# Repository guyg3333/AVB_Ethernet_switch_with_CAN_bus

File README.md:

# AVB_Ethernet_switch_with_CAN_bus

This PCB was made As part of an Academic engineering final project, the idea behind it is to offer a method of reorganizing information traffic in autonomous vehicles,

The problem I wanted to solve is how to expand the current communication method to support Advanced Drive assist application.

The proposed solution is to build a network built from a combination of CAN bus and Ethernet interfaces, were Ethernet used as backbone.

To do so I design and implement module that aim to manage data traffic and with him create a hierarchical Democratic multi master network were every node can exchange data.

To meet the requirements of critical information passing through a vehicle, the Ethernet switch ic supports the AVB protocol to Ensure real time policy.

The component was assimilated in Ben-Gurion University FSAE electric car in 2019

## PCB 3D Model

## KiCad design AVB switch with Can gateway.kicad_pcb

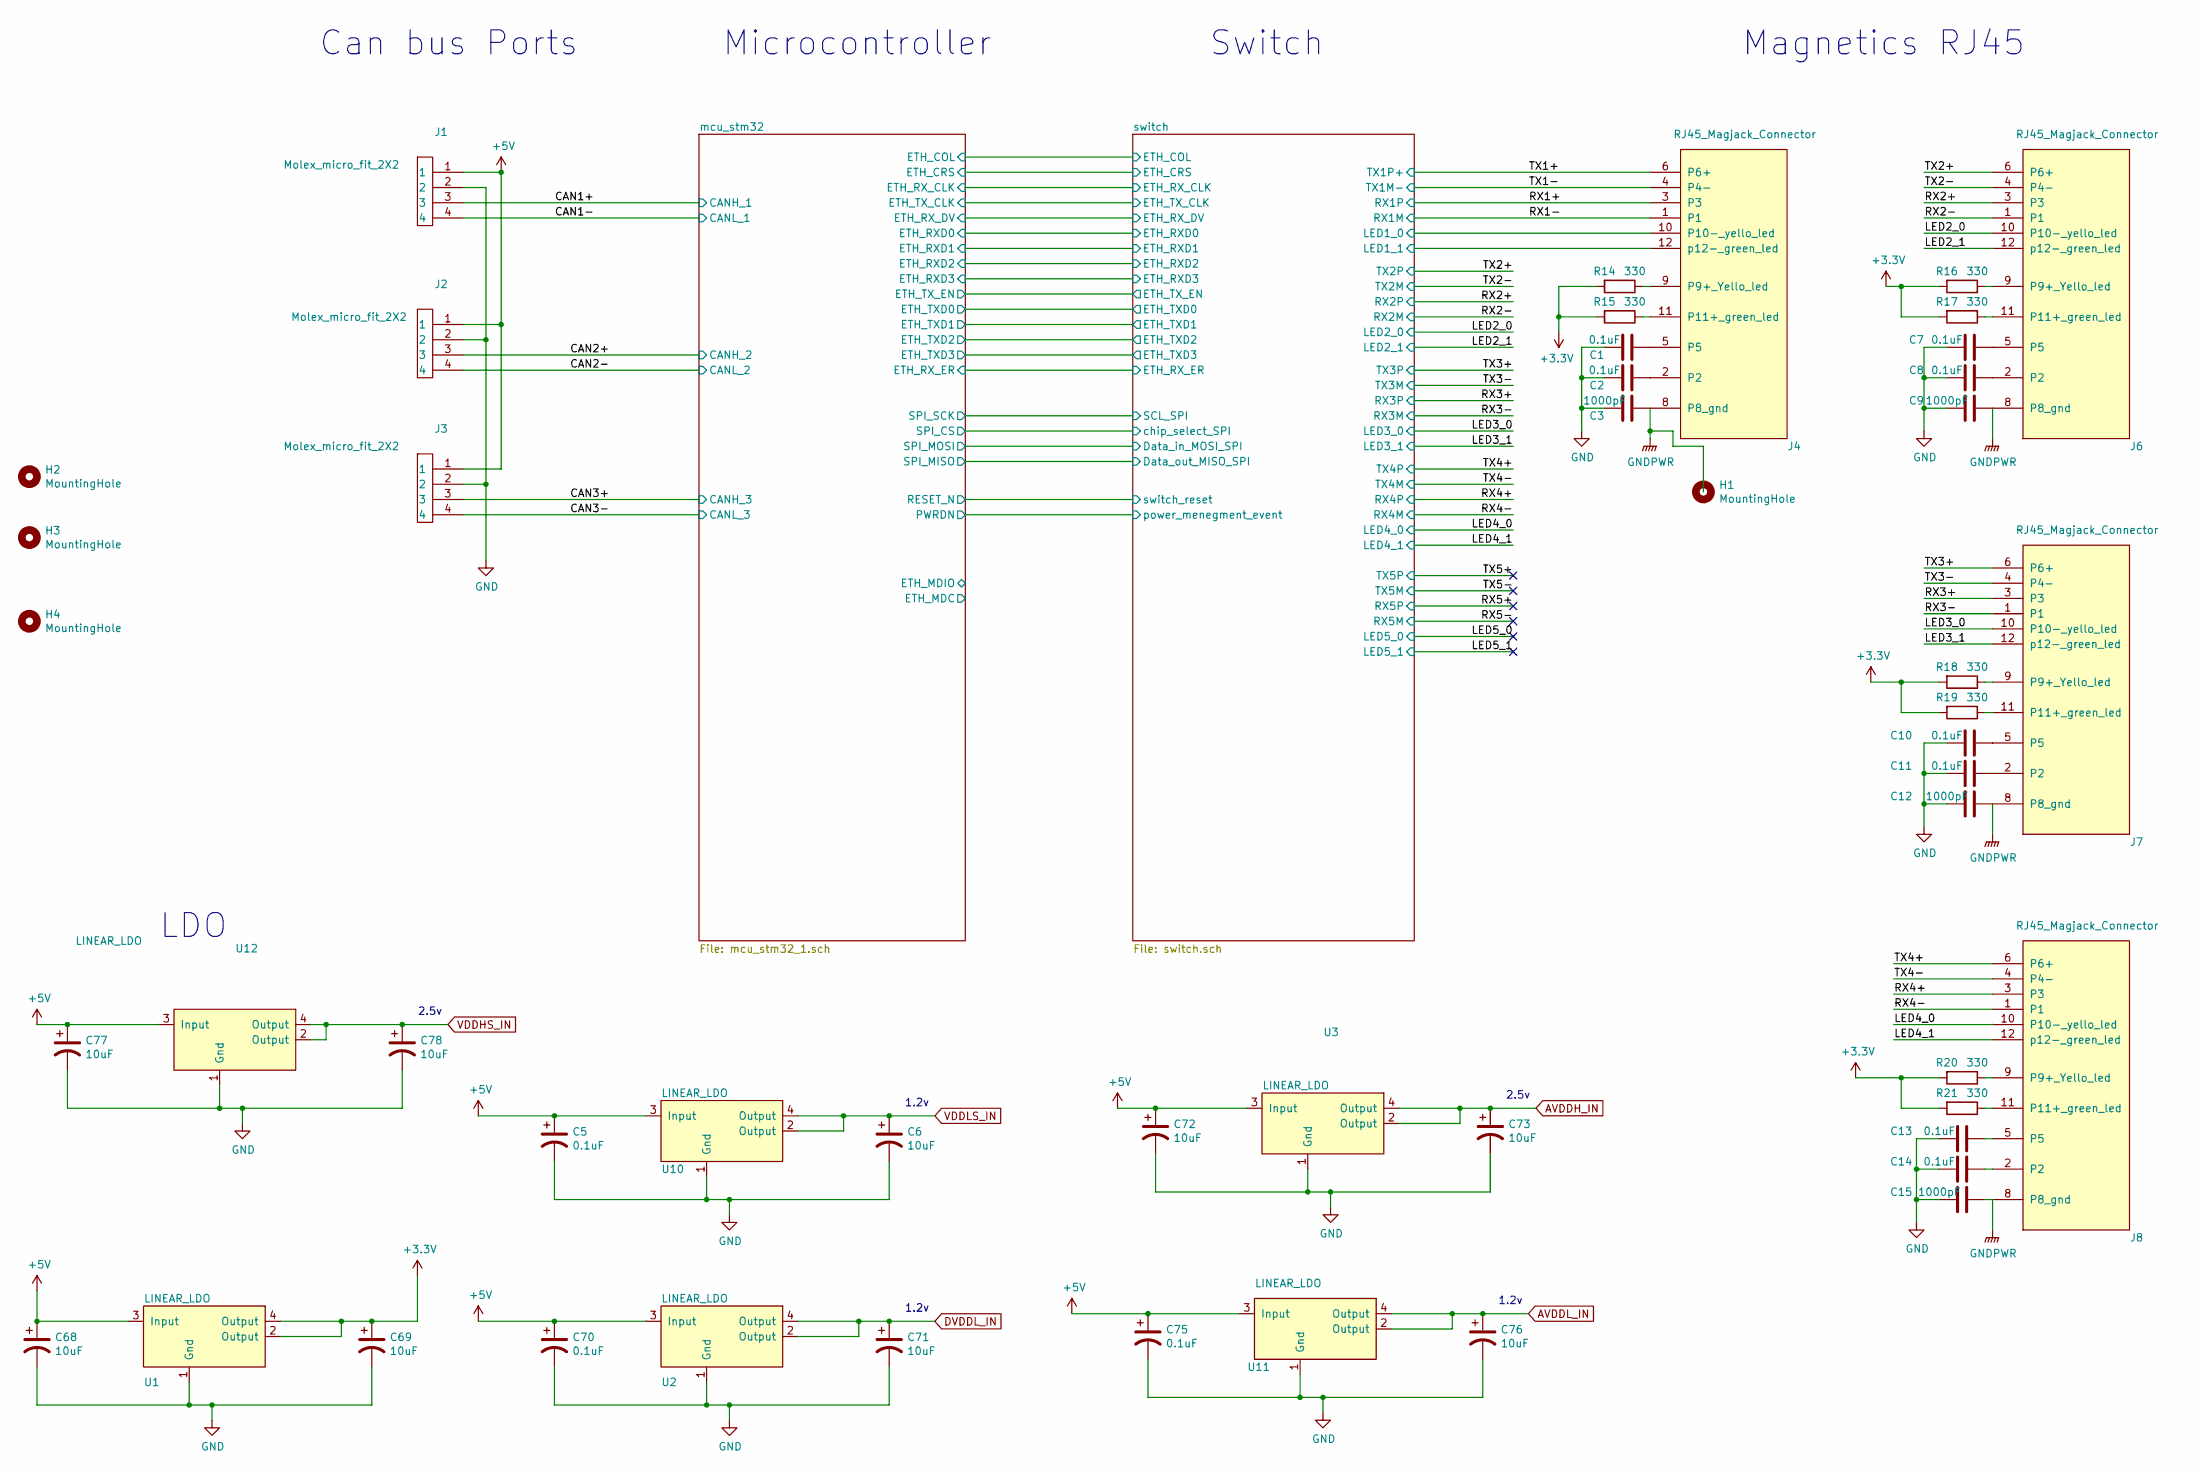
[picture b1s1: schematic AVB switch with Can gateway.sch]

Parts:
C1, C2, C7, C8, C10, C11, C13, C14: 0.1uF; C_0603_1608Metric_Pad1.05x0.95mm_HandSolder; Manufacturer_Part_Number C0603C104J4RACTU‎‏
C3, C9, C12, C15: 1000pF; C_0603_1608Metric_Pad1.05x0.95mm_HandSolder; Manufacturer_Part_Number C0603V102KDRAC7867‎‏
C5, C70, C75: 0.1uF; C_0603_1608Metric_Pad1.05x0.95mm_HandSolder; Manufacturer_Part_Number CC1206KRX7R9BB104‎‏
C6, C68, C69, C71, C72, C73, C76, C77, C78: 10uF; C_0603_1608Metric_Pad1.05x0.95mm_HandSolder; Manufacturer_Part_Number T520A106M010ATE080‎‏
H1, H2, H3, H4: MountingHole; 1pin
J1, J2, J3: Molex_micro_fit_2X2; Manufacturer_Part_Number ‏‎CONN HEADER VERT 4POS 3MM‎‏
J4, J6, J7, J8: RJ45_Magjack_Connector; RJ45_MAGJACK_1PORT_100_BASE-T‎‏; Manufacturer_Part_Number ‏‎JD2-0010NL‎‏
R14, R15, R16, R17, R18, R19, R20, R21: 330; R_0603_1608Metric_Pad1.05x0.95mm_HandSolder; Manufacturer_Part_Number ‏‎CR0603-JW-331ELF‎‏
U1: LINEAR_LDO; SOT-223; Manufacturer_Part_Number NCP1117ST33T3G‎‏
U2, U10, U11: LINEAR_LDO; SOT-223; Manufacturer_Part_Number LD1117AS12TR‎‏
U3, U12: LINEAR_LDO; SOT-223; Manufacturer_Part_Number ‏‎NCV1117ST25T3G‎‏

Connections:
+3V3: C69.1, R14.2, R15.2, R16.2, R17.2, R18.2, R19.2, R20.2, R21.2, U1.2 (Output), U1.4 (Output); also elsewhere on the board
+5V: C5.1, C68.1, C70.1, C72.1, C75.1, C77.1, J1.1, J2.1, J3.1, U1.3 (Input), U2.3 (Input), U3.3 (Input), U10.3 (Input), U11.3 (Input), U12.3 (Input)
/CAN1+: J1.3; also elsewhere on the board
/CAN1-: J1.4; also elsewhere on the board
/CAN2+: J2.3; also elsewhere on the board
/CAN2-: J2.4; also elsewhere on the board
/CAN3+: J3.3; also elsewhere on the board
/CAN3-: J3.4; also elsewhere on the board
/LED2_0: J6.10 (P10-_yello_led); also elsewhere on the board
/LED2_1: J6.12 (p12-_green_led); also elsewhere on the board
/LED3_0: J7.10 (P10-_yello_led); also elsewhere on the board
/LED3_1: J7.12 (p12-_green_led); also elsewhere on the board
/LED4_0: J8.10 (P10-_yello_led); also elsewhere on the board
/LED4_1: J8.12 (p12-_green_led); also elsewhere on the board
/RX1+: J4.3; also elsewhere on the board
/RX1-: J4.1; also elsewhere on the board
/RX2+: J6.3; also elsewhere on the board
/RX2-: J6.1; also elsewhere on the board
/RX3+: J7.3; also elsewhere on the board
/RX3-: J7.1; also elsewhere on the board
/RX4+: J8.3; also elsewhere on the board
/RX4-: J8.1; also elsewhere on the board
/TX1+: J4.6 (P6+); also elsewhere on the board
/TX1-: J4.4 (P4-); also elsewhere on the board
/TX2+: J6.6 (P6+); also elsewhere on the board
/TX2-: J6.4 (P4-); also elsewhere on the board
/TX3+: J7.6 (P6+); also elsewhere on the board
/TX3-: J7.4 (P4-); also elsewhere on the board
/TX4+: J8.6 (P6+); also elsewhere on the board
/TX4-: J8.4 (P4-); also elsewhere on the board
/switch/LED1_0: J4.10 (P10-_yello_led); also elsewhere on the board
/switch/LED1_1: J4.12 (p12-_green_led); also elsewhere on the board
AVDDH_IN: C73.1, U3.2 (Output), U3.4 (Output); also elsewhere on the board
AVDDL_IN: C76.1, U11.2 (Output), U11.4 (Output); also elsewhere on the board
DVDDL_IN: C71.1, U2.2 (Output), U2.4 (Output); also elsewhere on the board
GND: C1.2, C2.2, C3.2, C5.2, C6.2, C7.2, C8.2, C9.2, C10.2, C11.2, C12.2, C13.2, C14.2, C15.2, C68.2, C69.2, C70.2, C71.2, C72.2, C73.2, C75.2, C76.2, C77.2, C78.2, J1.2, J2.2, J3.2, U1.1 (Gnd), U2.1 (Gnd), U3.1 (Gnd), U10.1 (Gnd), U11.1 (Gnd), U12.1 (Gnd); also elsewhere on the board
GNDPWR: C3.1, C9.1, C12.1, C15.1, J4.8 (P8_gnd), J6.8 (P8_gnd), J7.8 (P8_gnd), J8.8 (P8_gnd)
unnamed: C1.1, J4.5
unnamed: C2.1, J4.2
unnamed: C7.1, J6.5
unnamed: C8.1, J6.2
unnamed: C10.1, J7.5
unnamed: C11.1, J7.2
unnamed: C13.1, J8.5
unnamed: C14.1, J8.2
unnamed: J4.9 (P9+_Yello_led), R14.1
unnamed: J4.11 (P11+_green_led), R15.1
unnamed: J6.9 (P9+_Yello_led), R16.1
unnamed: J6.11 (P11+_green_led), R17.1
unnamed: J7.9 (P9+_Yello_led), R18.1
unnamed: J7.11 (P11+_green_led), R19.1
unnamed: J8.9 (P9+_Yello_led), R20.1
unnamed: J8.11 (P11+_green_led), R21.1
VDDHS_IN: C78.1, U12.2 (Output), U12.4 (Output); also elsewhere on the board
VDDLS_IN: C6.1, U10.2 (Output), U10.4 (Output); also elsewhere on the board

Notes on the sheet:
Switch
Microcontroller
Can bus Ports
Magnetics RJ45
LDO
2.5v
1.2v

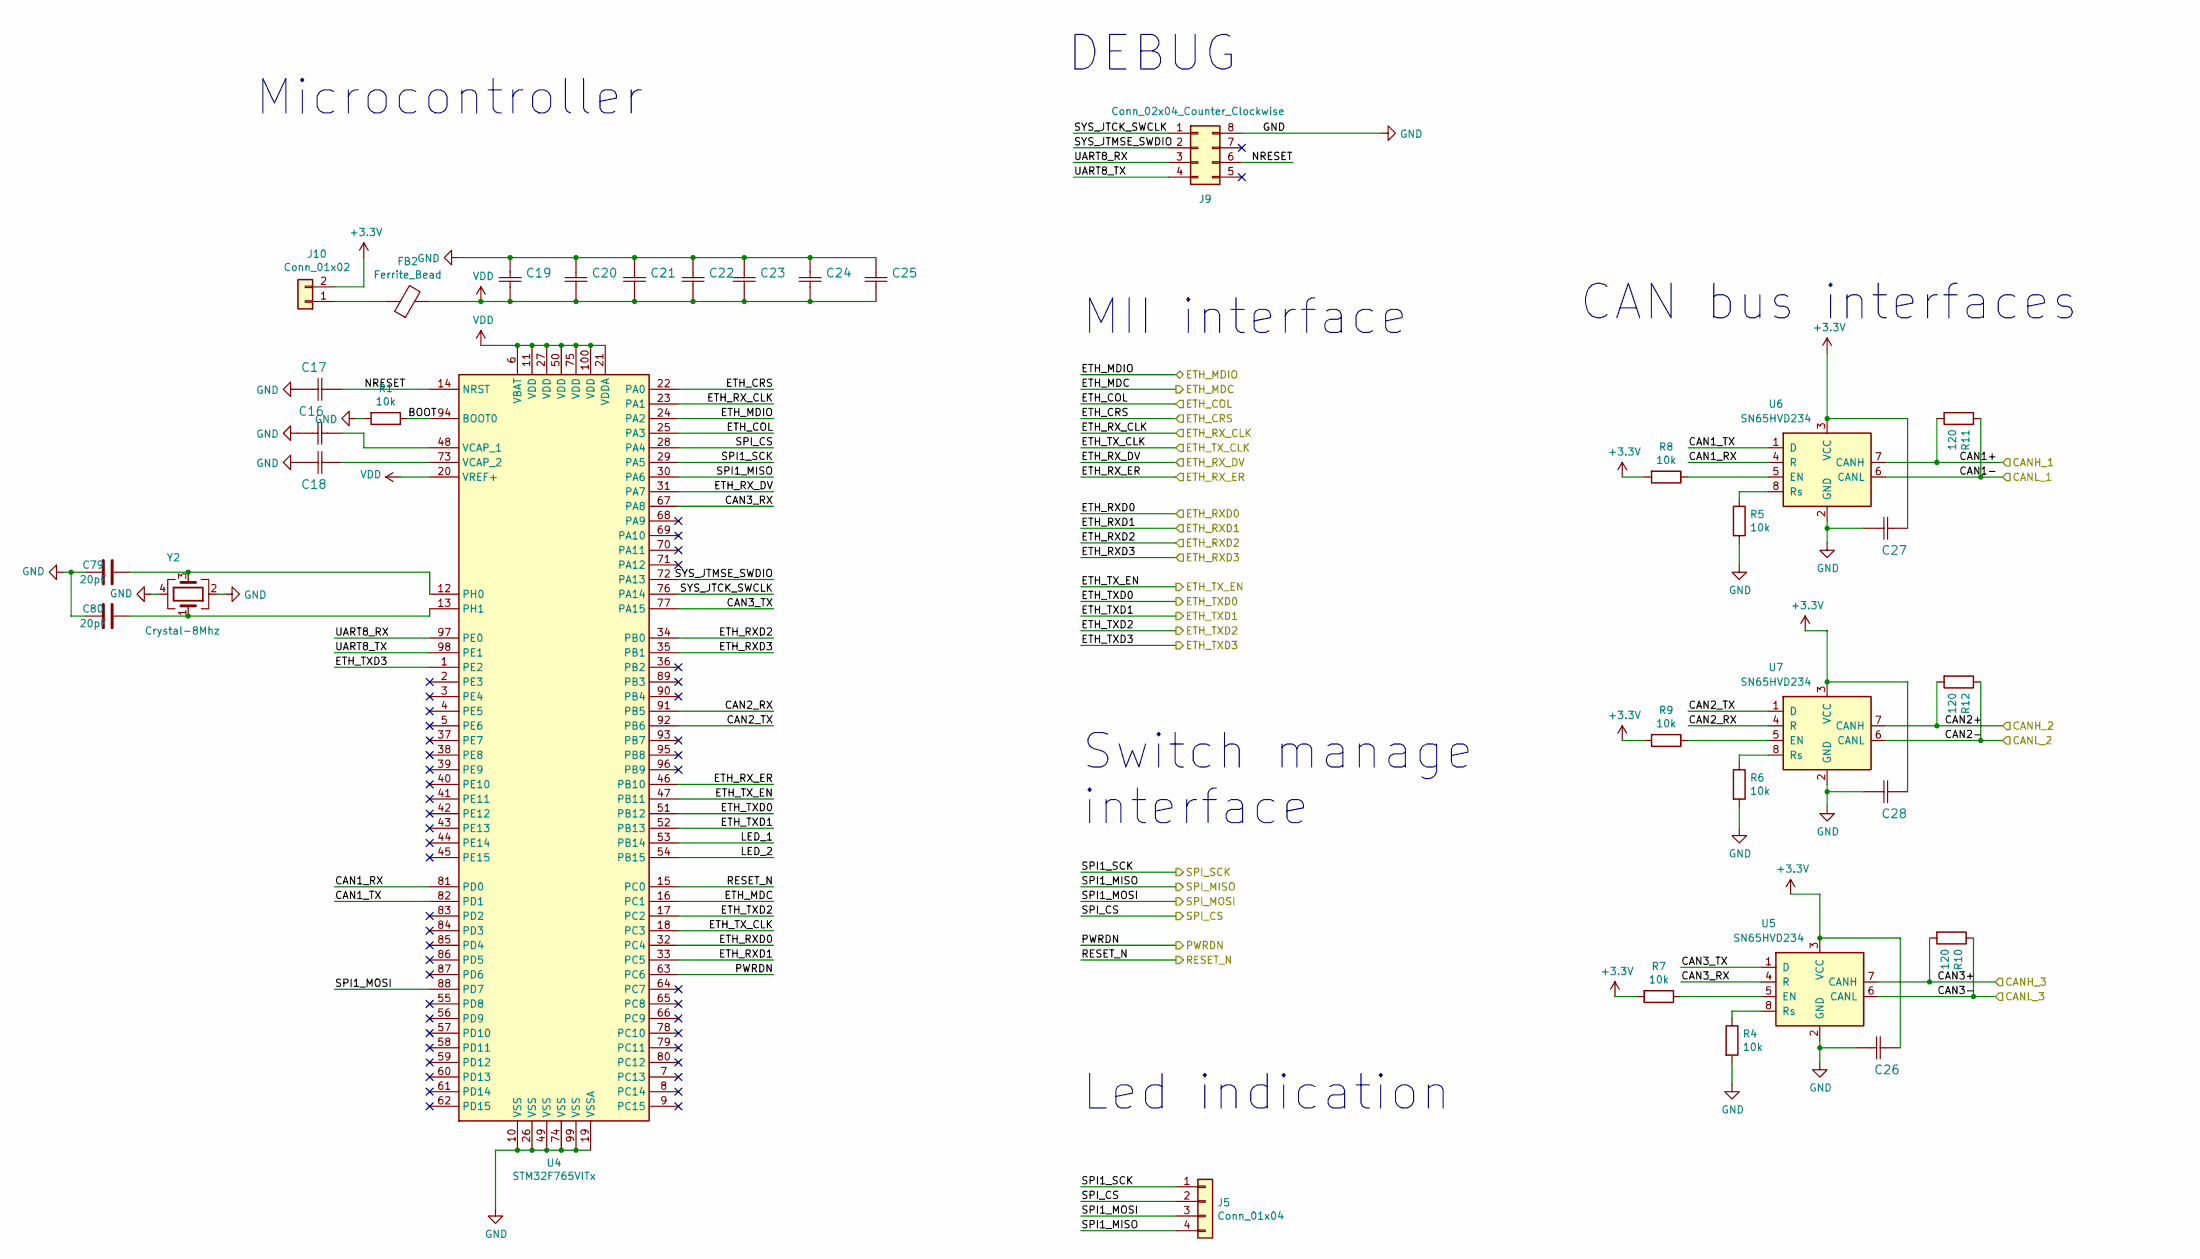
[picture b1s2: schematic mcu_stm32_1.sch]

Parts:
C16, C18, C26, C27, C28: 2.2uF; C_0603_1608Metric_Pad1.05x0.95mm_HandSolder; Manufacturer_Part_Number CL10A225KP8NNNC‎‏
C17, C20, C21, C22, C23, C24, C25: 0.1uF; C_0603_1608Metric_Pad1.05x0.95mm_HandSolder; Manufacturer_Part_Number C0603C104J4RACTU‎‏
C19: 4.7uF; C_0603_1608Metric_Pad1.05x0.95mm_HandSolder; Manufacturer_Part_Number CL10B475KQ8NQNC‎‏
C79, C80: 20pF; C_0603_1608Metric_Pad1.05x0.95mm_HandSolder; Manufacturer_Part_Number CL10C360JB8NNNC‎‏
FB2: Ferrite_Bead; C_0603_1608Metric_Pad1.05x0.95mm_HandSolder
J5: Conn_01x04; PinHeader_1x04_P2.54mm_Vertical
J9: Conn_02x04_Counter_Clockwise; PinHeader_2x04_P2.54mm_Vertical
J10: Conn_01x02; PinHeader_1x02_P2.54mm_Vertical
R1: 10k; R_0603_1608Metric_Pad1.05x0.95mm_HandSolder
R4, R5, R6, R7, R8, R9: 10k; R_0603_1608Metric_Pad1.05x0.95mm_HandSolder; Manufacturer_Part_Number RNCP0603FTD10K0‎‏
R10, R11, R12: 120; R_0603_1608Metric_Pad1.05x0.95mm_HandSolder; Manufacturer_Part_Number ‏‎CRGCQ0603F120R‎‏
U4: STM32F765VITx; LQFP-100_14x14mm_P0.5mm; Manufacturer_Part_Number ‏‎STM32F765VIT6‎‏
U5, U6, U7: SN65HVD234; SOIC-8_3.9x4.9mm_P1.27mm; Manufacturer_Part_Number SN65HVD234DR‎‏
Y2: Crystal-8Mhz; Crystal_SMD_3225-4Pin_3.2x2.5mm; Manufacturer_Part_Number ‏‎ECS-80-10-30B-CWN-TR‎‏

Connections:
+3V3: C26.1, C27.1, C28.1, J10.2, R7.2, R8.2, R9.2, U5.3 (VCC), U6.3 (VCC), U7.3 (VCC); also elsewhere on the board
/CAN1+: R11.2, U6.7 (CANH); also elsewhere on the board
/CAN1-: R11.1, U6.6 (CANL); also elsewhere on the board
/CAN2+: R12.2, U7.7 (CANH); also elsewhere on the board
/CAN2-: R12.1, U7.6 (CANL); also elsewhere on the board
/CAN3+: R10.2, U5.7 (CANH); also elsewhere on the board
/CAN3-: R10.1, U5.6 (CANL); also elsewhere on the board
/mcu_stm32/BOOT: R1.1, U4.94 (BOOT0)
/mcu_stm32/CAN1_RX: U4.81 (PD0), U6.4 (R)
/mcu_stm32/CAN1_TX: U4.82 (PD1), U6.1 (D)
/mcu_stm32/CAN2_RX: U4.91 (PB5), U7.4 (R)
/mcu_stm32/CAN2_TX: U4.92 (PB6), U7.1 (D)
/mcu_stm32/CAN3_RX: U4.67 (PA8), U5.4 (R)
/mcu_stm32/CAN3_TX: U4.77 (PA15), U5.1 (D)
/mcu_stm32/ETH_COL: U4.25 (PA3); also elsewhere on the board
/mcu_stm32/ETH_CRS: U4.22 (PA0); also elsewhere on the board
/mcu_stm32/ETH_MDC: U4.16 (PC1)
/mcu_stm32/ETH_MDIO: U4.24 (PA2)
/mcu_stm32/ETH_RXD0: U4.32 (PC4); also elsewhere on the board
/mcu_stm32/ETH_RXD1: U4.33 (PC5); also elsewhere on the board
/mcu_stm32/ETH_RXD2: U4.34 (PB0); also elsewhere on the board
/mcu_stm32/ETH_RXD3: U4.35 (PB1); also elsewhere on the board
/mcu_stm32/ETH_RX_CLK: U4.23 (PA1); also elsewhere on the board
/mcu_stm32/ETH_RX_DV: U4.31 (PA7); also elsewhere on the board
/mcu_stm32/ETH_RX_ER: U4.46 (PB10); also elsewhere on the board
/mcu_stm32/ETH_TXD0: U4.51 (PB12); also elsewhere on the board
/mcu_stm32/ETH_TXD1: U4.52 (PB13); also elsewhere on the board
/mcu_stm32/ETH_TXD2: U4.17 (PC2); also elsewhere on the board
/mcu_stm32/ETH_TXD3: U4.1 (PE2); also elsewhere on the board
/mcu_stm32/ETH_TX_CLK: U4.18 (PC3); also elsewhere on the board
/mcu_stm32/ETH_TX_EN: U4.47 (PB11); also elsewhere on the board
/mcu_stm32/LED_1: U4.53 (PB14)
/mcu_stm32/LED_2: U4.54 (PB15)
/mcu_stm32/NRESET: C17.1, J9.6, U4.14 (NRST)
/mcu_stm32/PWRDN: U4.63 (PC6)
/mcu_stm32/RESET_N: U4.15 (PC0); also elsewhere on the board
/mcu_stm32/SPI_CS: J5.2, U4.28 (PA4); also elsewhere on the board
/mcu_stm32/SYS_JTCK_SWCLK: J9.1, U4.76 (PA14)
/mcu_stm32/SYS_JTMSE_SWDIO: J9.2, U4.72 (PA13)
/mcu_stm32/UART8_RX: J9.3, U4.97 (PE0)
/mcu_stm32/UART8_TX: J9.4, U4.98 (PE1)
/switch/Data_in_MOSI_SPI: J5.3, U4.88 (PD7); also elsewhere on the board
/switch/Data_out_MISO_SPI: J5.4, U4.30 (PA6); also elsewhere on the board
/switch/SCL_SPI: J5.1, U4.29 (PA5); also elsewhere on the board
GND: C16.1, C17.2, C18.2, C19.1, C20.1, C21.1, C22.1, C23.1, C24.1, C25.1, C26.2, C27.2, C28.2, C79.2, C80.2, J9.8, R1.2, R4.2, R5.2, R6.2, U4.10 (VSS), U4.19 (VSSA), U4.26 (VSS), U4.49 (VSS), U4.74 (VSS), U4.99 (VSS), U5.2 (GND), U6.2 (GND), U7.2 (GND), Y2.2, Y2.4; also elsewhere on the board
unnamed: C16.2, U4.48 (VCAP_1)
unnamed: C18.1, U4.73 (VCAP_2)
unnamed: C79.1, U4.12 (PH0), Y2.3
unnamed: C80.1, U4.13 (PH1), Y2.1
unnamed: FB2.1, J10.1
unnamed: R4.1, U5.8 (Rs)
unnamed: R5.1, U6.8 (Rs)
unnamed: R6.1, U7.8 (Rs)
unnamed: R7.1, U5.5 (EN)
unnamed: R8.1, U6.5 (EN)
unnamed: R9.1, U7.5 (EN)
VDD: C19.2, C20.2, C21.2, C22.2, C23.2, C24.2, C25.2, FB2.2, U4.6 (VBAT), U4.11 (VDD), U4.20 (VREF+), U4.21 (VDDA), U4.27 (VDD), U4.50 (VDD), U4.75 (VDD), U4.100 (VDD)

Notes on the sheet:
DEBUG
MII interface
CAN bus interfaces
Microcontroller
Switch manage interface
Led indication

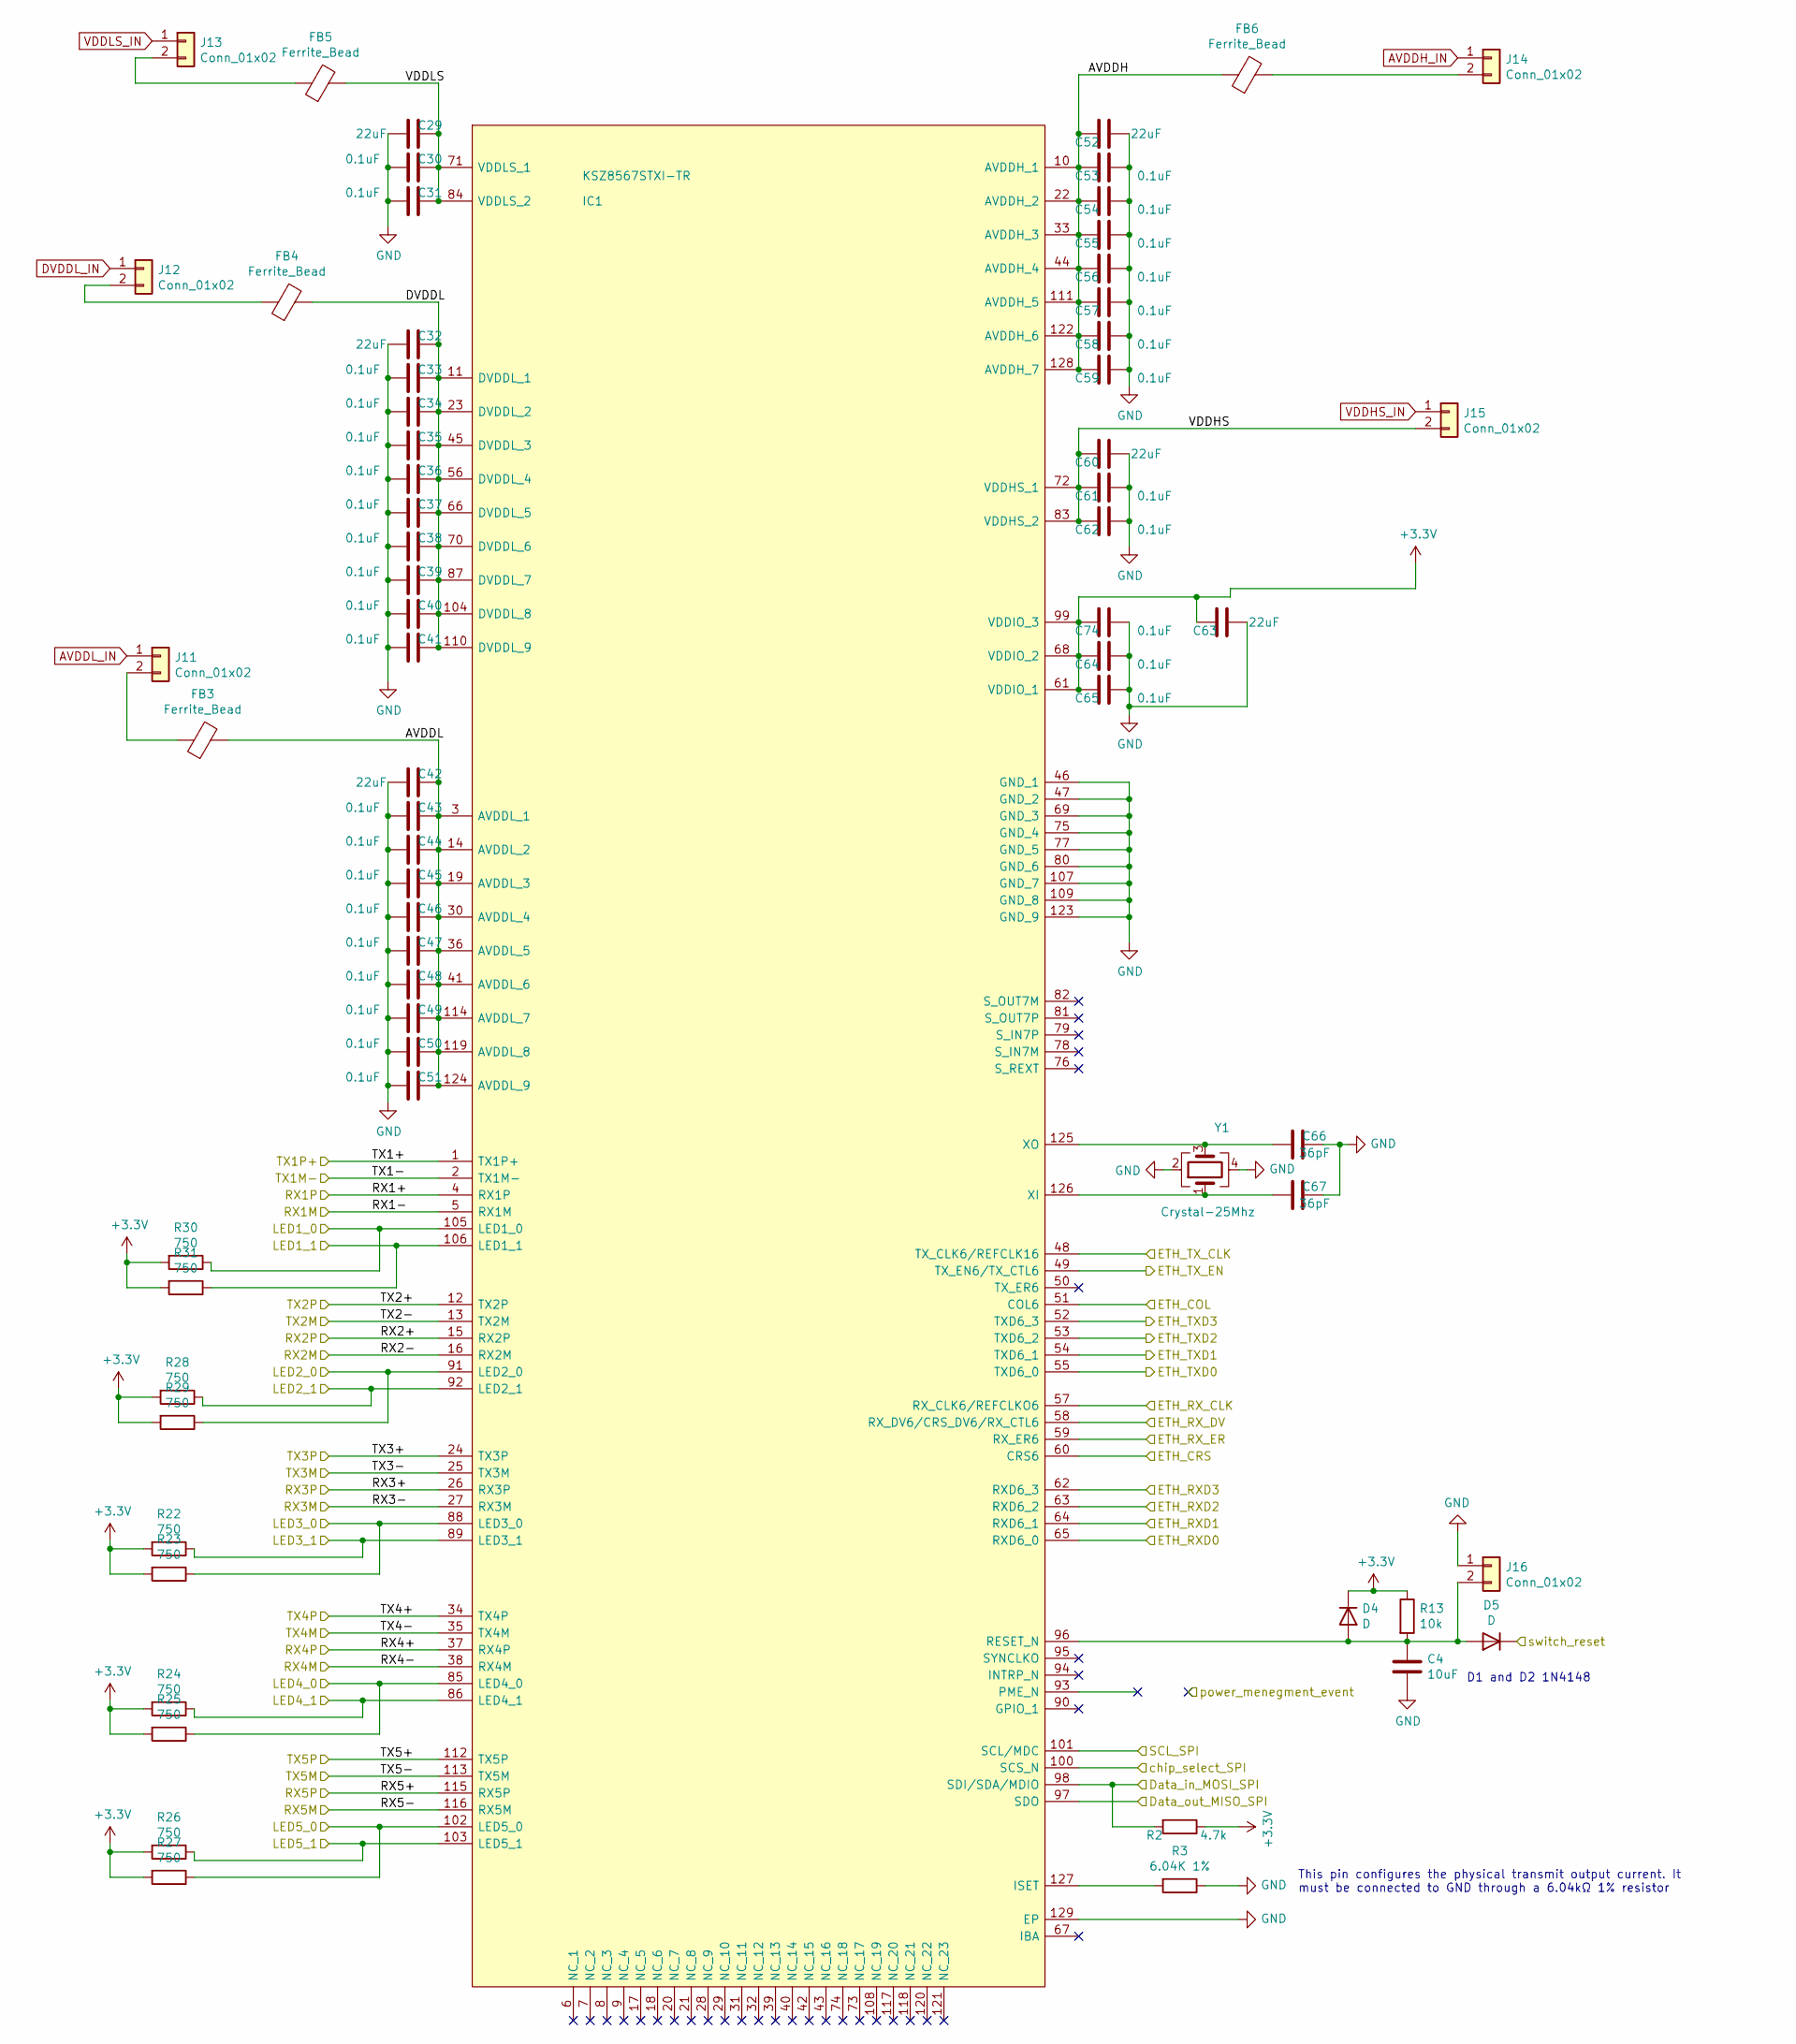
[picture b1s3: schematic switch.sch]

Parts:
C4: 10uF; C_0603_1608Metric_Pad1.05x0.95mm_HandSolder; Manufacturer_Part_Number CL10A106MQ8NNNC‎‏
C29, C32, C42, C52, C60, C63: 22uF; C_0603_1608Metric_Pad1.05x0.95mm_HandSolder; Manufacturer_Part_Number C1608X5R0J226M080AC‎‏
C30, C31, C33, C34, C35, C36, C37, C38, C39, C40, C41, C43, C44, C45, C46, C47, C48, C49, C50, C51, C53, C54, C55, C56, C57, C58, C59, C61, C62, C64, C65, C74: 0.1uF; C_0603_1608Metric_Pad1.05x0.95mm_HandSolder; Manufacturer_Part_Number C0603C104J4RACTU‎‏
C66, C67: 36pF; C_0603_1608Metric_Pad1.05x0.95mm_HandSolder; Manufacturer_Part_Number CL10C360JB8NNNC‎‏
D4, D5: D; D_SOD-323_HandSoldering; Manufacturer_Part_Number 1N4148WXTPMSCT
FB3, FB4, FB5, FB6: Ferrite_Bead; C_0603_1608Metric_Pad1.05x0.95mm_HandSolder
IC1: KSZ8567STXI-TR; QFP40P1600X1600X120-129N; Mouser Part Number 579-KSZ8567STXI-TR
J11, J12, J13, J14, J15, J16: Conn_01x02; PinHeader_1x02_P2.54mm_Vertical
R2: 4.7k; R_0603_1608Metric_Pad1.05x0.95mm_HandSolder; Manufacturer_Part_Number ‏‎RC0603JR-074K7L‎‏
R3: 6.04K 1%; R_0603_1608Metric_Pad1.05x0.95mm_HandSolder; Manufacturer_Part_Number RMCF0603FT6K04‎‏
R13: 10k; R_0603_1608Metric_Pad1.05x0.95mm_HandSolder; Manufacturer_Part_Number RNCP0603FTD10K0‎‏
R22, R23, R24, R25, R26, R27, R28, R29, R30, R31: 750; R_0603_1608Metric_Pad1.05x0.95mm_HandSolder
Y1: Crystal-25Mhz; Crystal_SMD_3225-4Pin_3.2x2.5mm; Manufacturer_Part_Number ‏‎FA-238 25.0000MB-C3‎‏

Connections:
+3V3: C63.1, C64.1, C65.1, C74.1, D4.1 (K), IC1.61 (VDDIO_1), IC1.68 (VDDIO_2), IC1.99 (VDDIO_3), R2.1, R13.1, R22.2, R23.2, R24.2, R25.2, R26.2, R27.2, R28.2, R29.2, R30.2, R31.2; also elsewhere on the board
/LED2_0: IC1.91 (LED2_0), R29.1; also elsewhere on the board
/LED2_1: IC1.92 (LED2_1), R28.1; also elsewhere on the board
/LED3_0: IC1.88 (LED3_0), R23.1; also elsewhere on the board
/LED3_1: IC1.89 (LED3_1), R22.1; also elsewhere on the board
/LED4_0: IC1.85 (LED4_0), R25.1; also elsewhere on the board
/LED4_1: IC1.86 (LED4_1), R24.1; also elsewhere on the board
/LED5_0: IC1.102 (LED5_0), R27.1
/LED5_1: IC1.103 (LED5_1), R26.1
/RX1+: IC1.4 (RX1P); also elsewhere on the board
/RX1-: IC1.5 (RX1M); also elsewhere on the board
/RX2+: IC1.15 (RX2P); also elsewhere on the board
/RX2-: IC1.16 (RX2M); also elsewhere on the board
/RX3+: IC1.26 (RX3P); also elsewhere on the board
/RX3-: IC1.27 (RX3M); also elsewhere on the board
/RX4+: IC1.37 (RX4P); also elsewhere on the board
/RX4-: IC1.38 (RX4M); also elsewhere on the board
/RX5+: IC1.115 (RX5P)
/RX5-: IC1.116 (RX5M)
/TX1+: IC1.1 (TX1P+); also elsewhere on the board
/TX1-: IC1.2 (TX1M-); also elsewhere on the board
/TX2+: IC1.12 (TX2P); also elsewhere on the board
/TX2-: IC1.13 (TX2M); also elsewhere on the board
/TX3+: IC1.24 (TX3P); also elsewhere on the board
/TX3-: IC1.25 (TX3M); also elsewhere on the board
/TX4+: IC1.34 (TX4P); also elsewhere on the board
/TX4-: IC1.35 (TX4M); also elsewhere on the board
/TX5+: IC1.112 (TX5P)
/TX5-: IC1.113 (TX5M)
/mcu_stm32/ETH_COL: IC1.51 (COL6); also elsewhere on the board
/mcu_stm32/ETH_CRS: IC1.60 (CRS6); also elsewhere on the board
/mcu_stm32/ETH_RXD0: IC1.65 (RXD6_0); also elsewhere on the board
/mcu_stm32/ETH_RXD1: IC1.64 (RXD6_1); also elsewhere on the board
/mcu_stm32/ETH_RXD2: IC1.63 (RXD6_2); also elsewhere on the board
/mcu_stm32/ETH_RXD3: IC1.62 (RXD6_3); also elsewhere on the board
/mcu_stm32/ETH_RX_CLK: IC1.57 (RX_CLK6/REFCLKO6); also elsewhere on the board
/mcu_stm32/ETH_RX_DV: IC1.58 (RX_DV6/CRS_DV6/RX_CTL6); also elsewhere on the board
/mcu_stm32/ETH_RX_ER: IC1.59 (RX_ER6); also elsewhere on the board
/mcu_stm32/ETH_TXD0: IC1.55 (TXD6_0); also elsewhere on the board
/mcu_stm32/ETH_TXD1: IC1.54 (TXD6_1); also elsewhere on the board
/mcu_stm32/ETH_TXD2: IC1.53 (TXD6_2); also elsewhere on the board
/mcu_stm32/ETH_TXD3: IC1.52 (TXD6_3); also elsewhere on the board
/mcu_stm32/ETH_TX_CLK: IC1.48 (TX_CLK6/REFCLK16); also elsewhere on the board
/mcu_stm32/ETH_TX_EN: IC1.49 (TX_EN6/TX_CTL6); also elsewhere on the board
/mcu_stm32/RESET_N: D5.1 (K); also elsewhere on the board
/mcu_stm32/SPI_CS: IC1.100 (SCS_N); also elsewhere on the board
/switch/AVDDH: C52.1, C53.1, C54.1, C55.1, C56.1, C57.1, C58.1, C59.1, FB6.1, IC1.10 (AVDDH_1), IC1.22 (AVDDH_2), IC1.33 (AVDDH_3), IC1.44 (AVDDH_4), IC1.111 (AVDDH_5), IC1.122 (AVDDH_6), IC1.128 (AVDDH_7)
/switch/AVDDL: C42.1, C43.1, C44.1, C45.1, C46.1, C47.1, C48.1, C49.1, C50.1, C51.1, FB3.2, IC1.3 (AVDDL_1), IC1.14 (AVDDL_2), IC1.19 (AVDDL_3), IC1.30 (AVDDL_4), IC1.36 (AVDDL_5), IC1.41 (AVDDL_6), IC1.114 (AVDDL_7), IC1.119 (AVDDL_8), IC1.124 (AVDDL_9)
/switch/DVDDL: C32.1, C33.1, C34.1, C35.1, C36.1, C37.1, C38.1, C39.1, C40.1, C41.1, FB4.2, IC1.11 (DVDDL_1), IC1.23 (DVDDL_2), IC1.45 (DVDDL_3), IC1.56 (DVDDL_4), IC1.66 (DVDDL_5), IC1.70 (DVDDL_6), IC1.87 (DVDDL_7), IC1.104 (DVDDL_8), IC1.110 (DVDDL_9)
/switch/Data_in_MOSI_SPI: IC1.98 (SDI/SDA/MDIO), R2.2; also elsewhere on the board
/switch/Data_out_MISO_SPI: IC1.97 (SDO); also elsewhere on the board
/switch/LED1_0: IC1.105 (LED1_0), R30.1; also elsewhere on the board
/switch/LED1_1: IC1.106 (LED1_1), R31.1; also elsewhere on the board
/switch/SCL_SPI: IC1.101 (SCL/MDC); also elsewhere on the board
/switch/VDDHS: C60.1, C61.1, C62.1, IC1.72 (VDDHS_1), IC1.83 (VDDHS_2), J15.2
/switch/VDDLS: C29.1, C30.1, C31.1, FB5.2, IC1.71 (VDDLS_1), IC1.84 (VDDLS_2)
AVDDH_IN: J14.1; also elsewhere on the board
AVDDL_IN: J11.1; also elsewhere on the board
DVDDL_IN: J12.1; also elsewhere on the board
GND: C4.2, C29.2, C30.2, C31.2, C32.2, C33.2, C34.2, C35.2, C36.2, C37.2, C38.2, C39.2, C40.2, C41.2, C42.2, C43.2, C44.2, C45.2, C46.2, C47.2, C48.2, C49.2, C50.2, C51.2, C52.2, C53.2, C54.2, C55.2, C56.2, C57.2, C58.2, C59.2, C60.2, C61.2, C62.2, C63.2, C64.2, C65.2, C66.2, C67.2, C74.2, IC1.46 (GND_1), IC1.47 (GND_2), IC1.69 (GND_3), IC1.75 (GND_4), IC1.77 (GND_5), IC1.80 (GND_6), IC1.107 (GND_7), IC1.109 (GND_8), IC1.123 (GND_9), IC1.129 (EP), J16.1, R3.1, Y1.2, Y1.4; also elsewhere on the board
unnamed: C4.1, D4.2 (A), D5.2 (A), IC1.96 (RESET_N), J16.2, R13.2
unnamed: C66.1, IC1.125 (XO), Y1.3
unnamed: C67.1, IC1.126 (XI), Y1.1
unnamed: FB3.1, J11.2
unnamed: FB4.1, J12.2
unnamed: FB5.1, J13.2
unnamed: FB6.2, J14.2
unnamed: IC1.127 (ISET), R3.2
VDDHS_IN: J15.1; also elsewhere on the board
VDDLS_IN: J13.1; also elsewhere on the board

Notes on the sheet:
This pin configures the physical transmit output current. It must be connected to GND through a 6.04kΩ 1% resistor
D1 and D2 1N4148

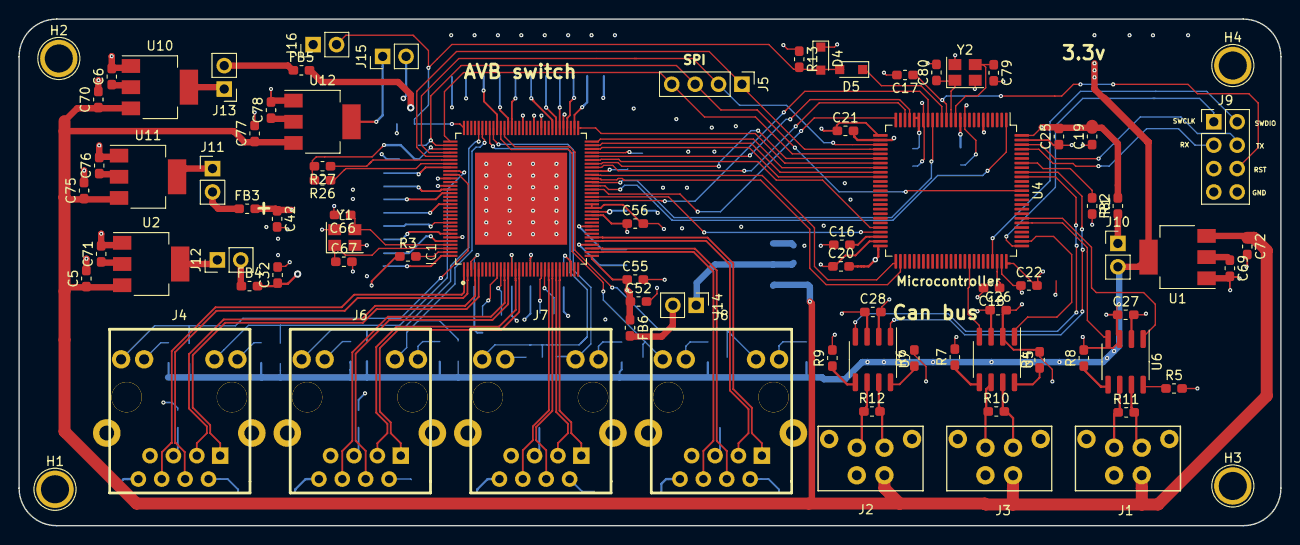
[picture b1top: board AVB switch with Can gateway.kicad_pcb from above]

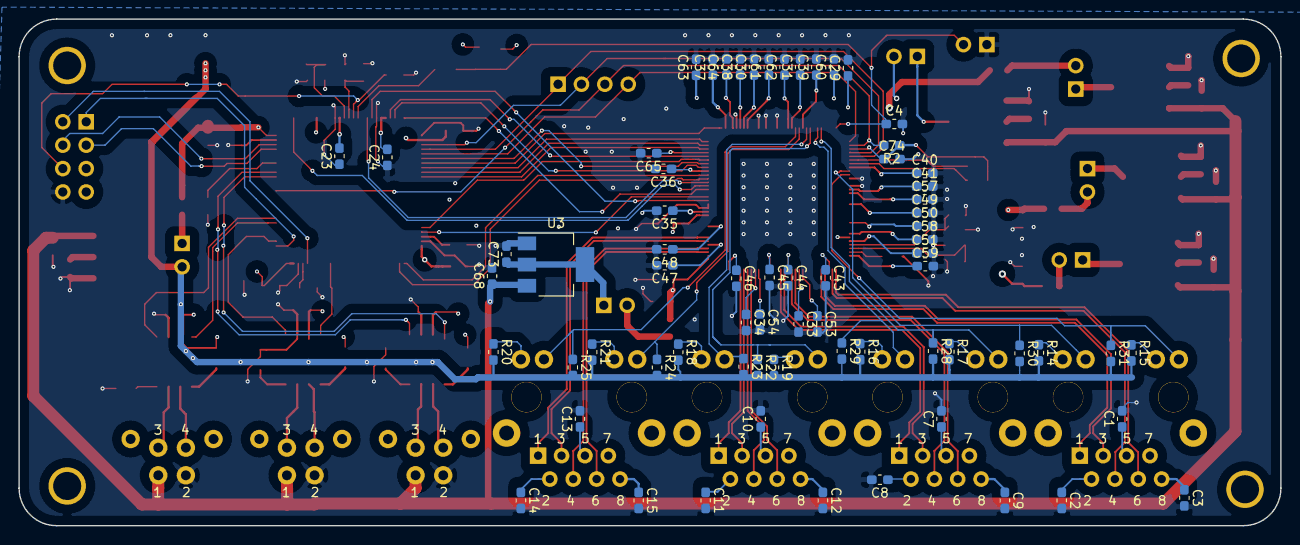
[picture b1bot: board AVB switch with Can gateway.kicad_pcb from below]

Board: 4 copper layers, 137.0 x 55.0 mm, 151 parts (68 on the bottom side), 114 nets.

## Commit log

2021-08-14 init the project
